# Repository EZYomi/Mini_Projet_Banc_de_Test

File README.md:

# Mini Projet Banc de Test

### Réalisé par mes soins 📌

Dans ce répertoire vous trouverez mes différents ficher de PCB ainsi que que de codage en langage C adapté Arduino. 

#### Matériel Utilisé 🧰

| Nom  🏷️    | Description 📖 |
| ----------- | ----------- |
| [LCD Hitachi](https://www.alldatasheet.com/datasheet-pdf/pdf/63673/HITACHI/HD44780.html)      | Ecran LCD en I2C       |
| [Beginner Kit Grove](https://www.gotronic.fr/art-beginner-kit-grove-110061162-31759.htm)      | Beginner Kit Grove de Seeedstudio spécialement prévu pour le monde de l'éducation proposant 12 projets Arduino reposants sur 10 modules Grove.       |
| [Broche Pogo](https://www.amazon.fr/Connecteurs-%C3%A9lectriques-Industriels-%C3%A9lectronique-Automobile/dp/B0F9LC9N87/ref=sr_1_18_sspa?__mk_fr_FR=%C3%85M%C3%85%C5%BD%C3%95%C3%91&crid=3KOYI9NY5HROW&dib=eyJ2IjoiMSJ9.8agn-p5RU884GjmctHngVaw38WZ8QR_x19pRdE1nuCrHeSdvz4q5IwNY3RV67dovoLLWUoWPLOadWBapfy3xcv7TXvfdvYMzYT3YVmWDnaX8qZfVgV1Zi2P-v6lGEjXEtML1IxxYgfLoKAuZ2CPc_V95-OBpd-mmGAkokWG-ELojFpAKphBq2-IrJhT4wf811Pz9_4ANHTz2h0NharQUT2y0uVdjxz91WWGvPjFvyl7G6qNUA6HCWjMKs9LSrpubqwIRaz7f5q0FzqJ6RuAYgDHNuwXUS2lEImtChZe6Hvo.dxwsfJOrP5SxurNdvKnmHxaJozR2LFn7prHrE1S2rZw&dib_tag=se&keywords=broche+pogo&qid=1790951161&sprefix=broche+pogo%2Caps%2C1325&sr=8-18-spons&aref=wVf9xaEqUO&sp_csd=d2lkZ2V0TmFtZT1zcF9tdGY&psc=1)      | Connecteur Facile d'utilisation      |
| [Liquid Crystal](https://docs.arduino.cc/libraries/liquidcrystal/)      | Bibliothèque Arduino. Cette bibliothèque permet à une carte Arduino/Genuino de contrôler des écrans LCD basés sur le chipset Hitachi HD44780 (ou compatible), présent dans la plupart des écrans LCD à affichage texte. Elle fonctionne en mode 4 ou 8 bits (c'est-à-dire en utilisant 4 ou 8 lignes de données en plus des lignes rs, enable et, éventuellement, rw de contrôle).       |

#### Feuille de route 🗃️

- [x] Imagination et conception du schéma et du PCB
- [x] Programmer en Langage C / Arduino
- [x] Prévoir une procédure de test complète
- [x] Versionnage du projet a l'aide de GIT
- [X] Création d'un README esthéthique et mise à jour

Pour plus d'information vous pouvez me contacter. [📑](https://mail.google.com/mail/u/0/?service=mail&flowName=GlifWebSignIn&flowEntry=AccountChooser&ec=asw-gmail-globalnav-signin#inbox?compose=new)

#### Merci d'avoir pris connaissance de ce répertoire traitant de mon Mini Projet

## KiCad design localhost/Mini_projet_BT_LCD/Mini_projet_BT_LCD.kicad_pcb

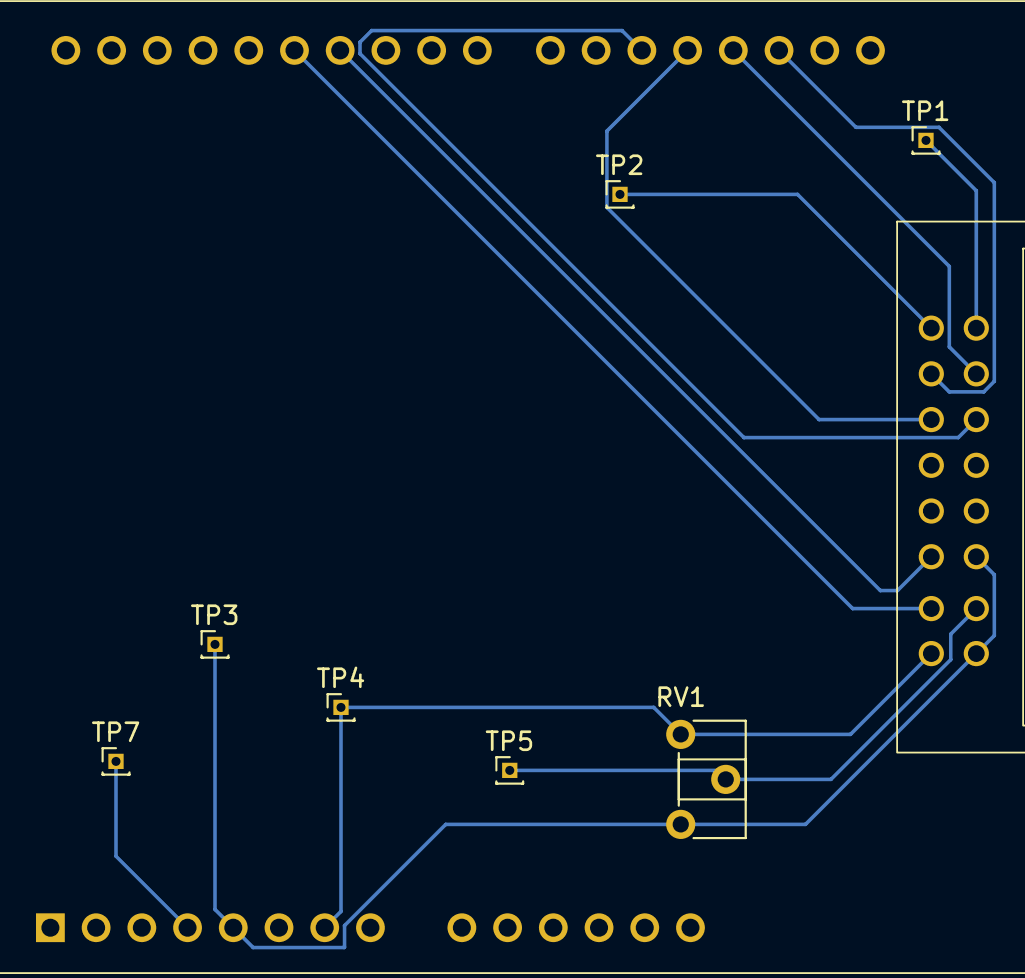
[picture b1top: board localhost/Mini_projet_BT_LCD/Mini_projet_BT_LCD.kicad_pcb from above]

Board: 2 copper layers, 8 parts (0 on the bottom side), 5 nets.

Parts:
LCD1: LCD
RV1: R_Potentiometer; Potentiometer_ACP_CA6-H2,5_Horizontal
TP1, TP2, TP3, TP4, TP5, TP7: TestPoint; PinHeader_1x01_P1.00mm_Vertical

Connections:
unnamed: LCD1.1 (VSS), LCD1.5 (R/W), RV1.3, TP3.1
unnamed: LCD1.15 (A), TP1.1
unnamed: LCD1.16 (K), TP2.1
unnamed: LCD1.2 (VDD), RV1.1, TP4.1
unnamed: LCD1.3 (VO), RV1.2, TP5.1

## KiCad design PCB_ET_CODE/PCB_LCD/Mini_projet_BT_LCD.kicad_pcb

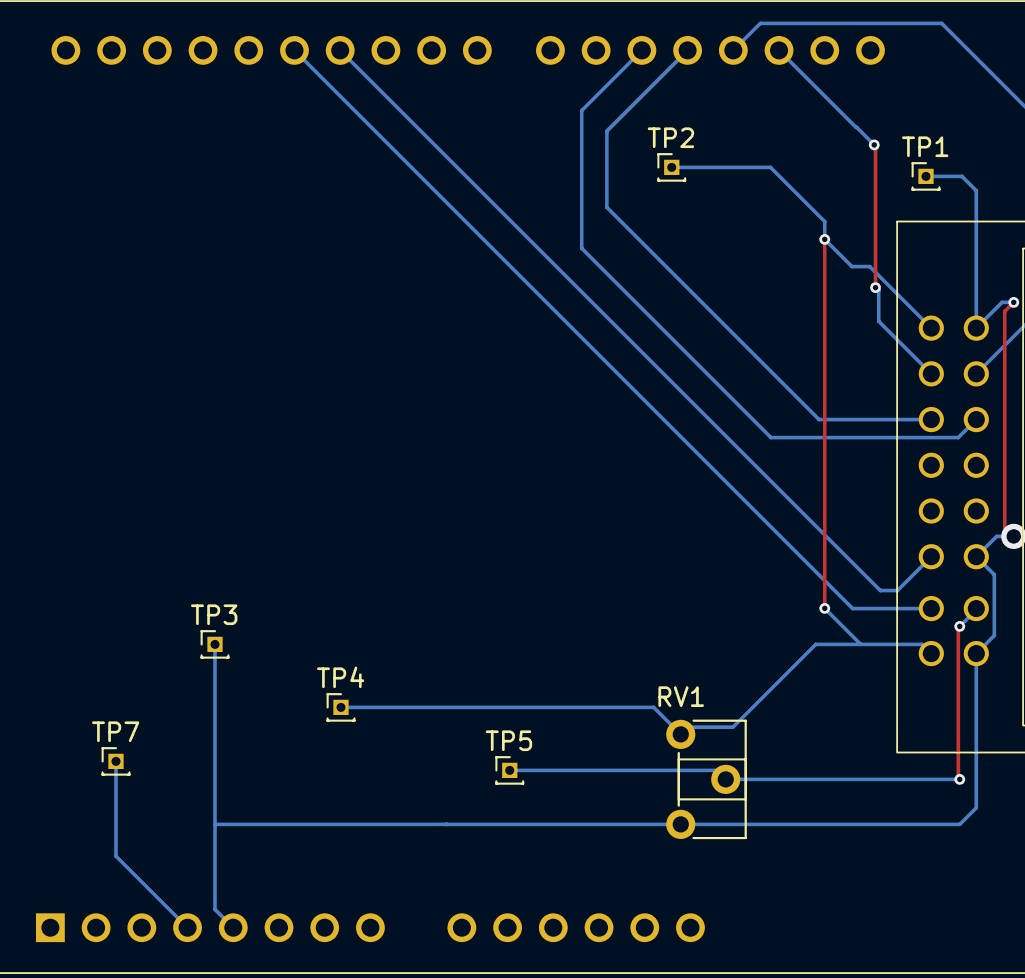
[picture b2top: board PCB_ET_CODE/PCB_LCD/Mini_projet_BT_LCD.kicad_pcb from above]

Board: 2 copper layers, 8 parts (0 on the bottom side), 3 nets.

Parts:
LCD1: LCD
RV1: R_Potentiometer; Potentiometer_ACP_CA6-H2,5_Horizontal
TP1, TP2, TP3, TP4, TP5, TP7: TestPoint; PinHeader_1x01_P1.00mm_Vertical

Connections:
unnamed: LCD1.1 (VSS), LCD1.5 (R/W), LCD1.15 (A), RV1.3, TP1.1, TP3.1
unnamed: LCD1.2 (VDD), LCD1.16 (K), RV1.1, TP2.1, TP4.1
unnamed: LCD1.3 (VO), RV1.2, TP5.1
